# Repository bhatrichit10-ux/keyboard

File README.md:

# keyboard
my own very little keyboard!

i think i need a new keyboard, so whynot make a new one. hehehe

Well, its my first ever keyboard after i made my micropad. (Using qmk for first time aswell)
## Features
- 60% keyboard - 60 keys
- made using qmk
- uses pi pico
- simple matrix design
- easy to recreate

## Schematics
Matrix: <br>
 <br>
Microcontroller: <br>
 <br>

## PCB Design

### PCB Checkout
<br>
<br>

```
Q: Why did i use Robu instead of JLCPCB or SEEED STUDIO FUSION?
A: I live in India and, Robu might be expensive at first but actually it is alot cheaper! Shipping costs to me from JLCPCB and SEEEDSTUDIO FUSION are around $15-$30. Whereas at a little expensive cost, i can get from Robu which is India based and avoid customs as well!

Also my home is like in a region where its harder to ship stuff so maybe robu might also charge extra
```

## CAD 
Case with PCB: <br>
 <br>
 <br>
 <br>
 <br>

## Firmware
I made the firmware using QMK. And compiled it in `firmware` directory

# BOM

|Name                                                          |Purpose         |Quantity|Total Cost (USD)|Distributor   |
|--------------------------------------------------------------|----------------|--------|----------------|--------------|
|RPI Pico                                                      |The brain       |1       |4.47            |RObu.in       |
|Diodes ( Pack of 70)                                          |Matrix Working  |7       |1.16            |Stacks KB     |
|PCB                                                           |Connect stuff   |1       |50.50           |Robu.in       |
|Counter Strike Printstream Decal Collection Cherry PBT Keycaps|Keycaps         |1       |18.07           |Curiosity Caps|
|Akko Botany Switch (Pack of 45)                               |Main Keyswicthes|2       |23.38           |Stacks KB     |

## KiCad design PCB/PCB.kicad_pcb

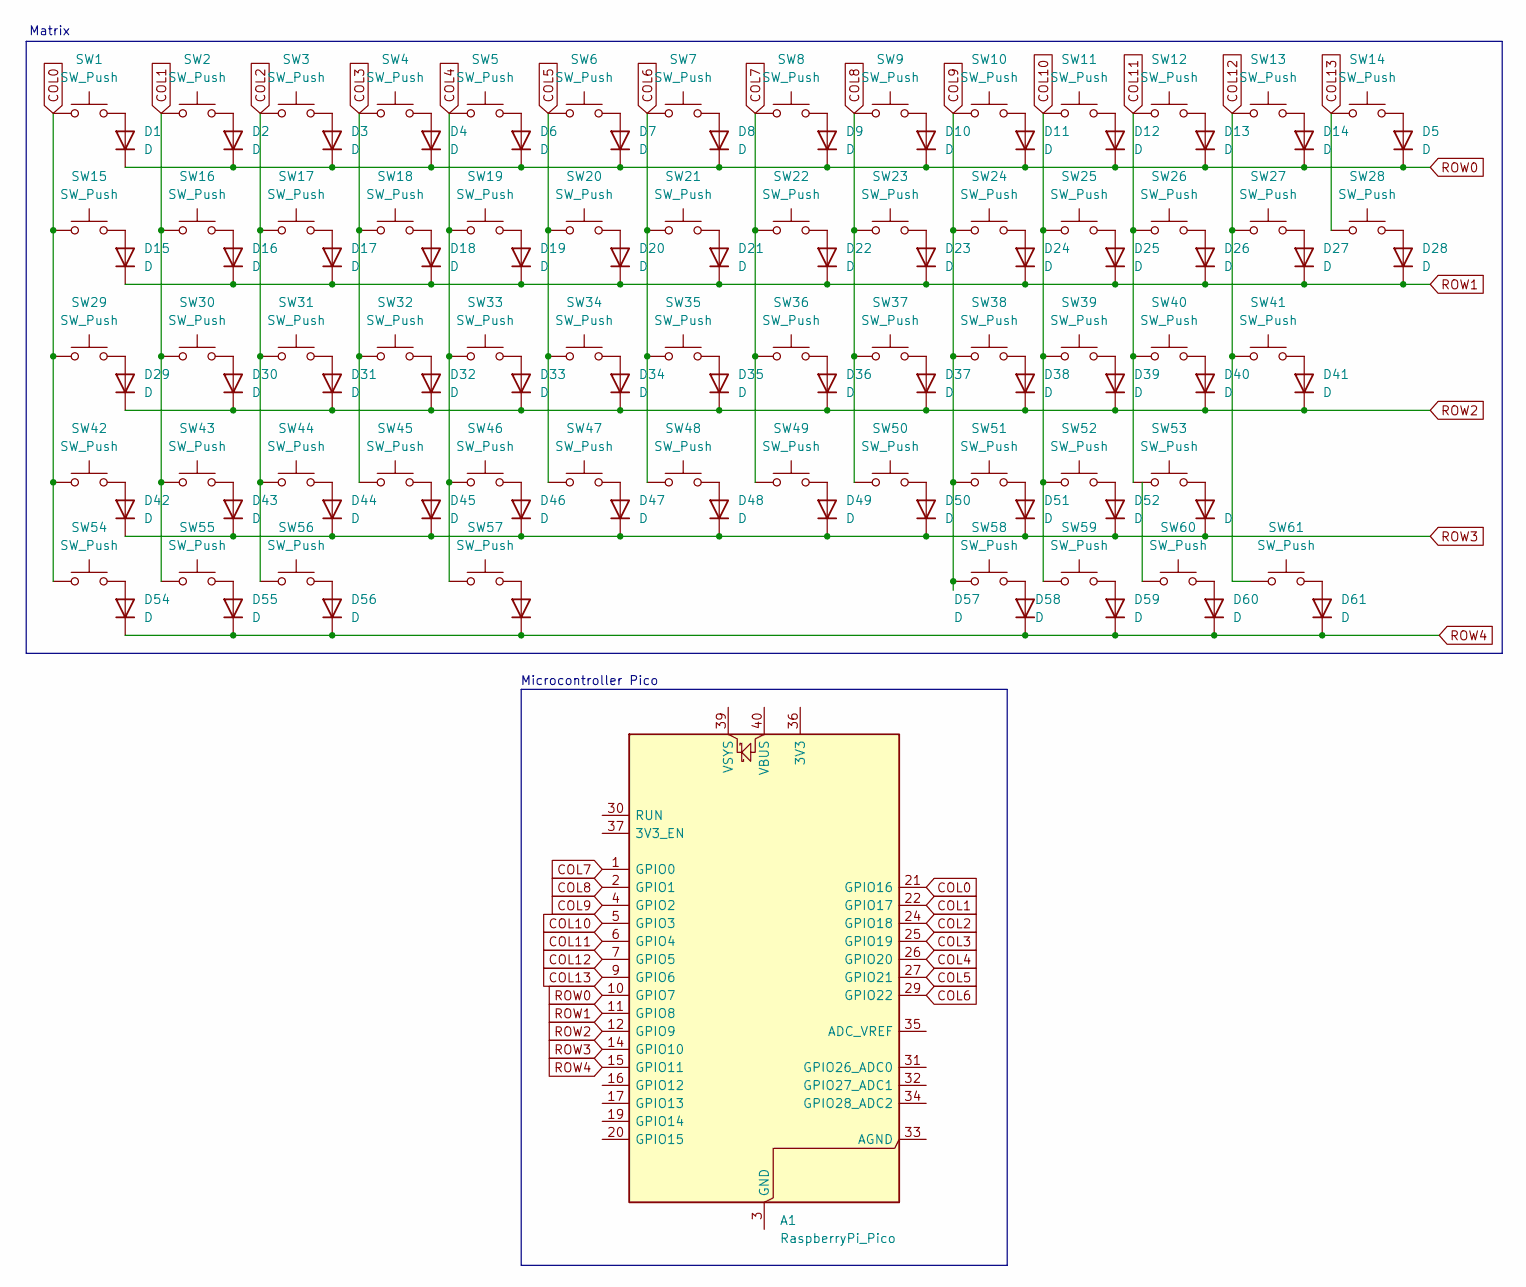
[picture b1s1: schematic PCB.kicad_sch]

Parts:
A1: RaspberryPi_Pico; RaspberryPi_Pico_Common_Unspecified
D1, D2, D3, D4, D5, D6, D7, D8, D9, D10, D11, D12, D13, D14, D15, D16, D17, D18, D19, D20, D21, D22, D23, D24, D25, D26, D27, D28, D29, D30, D31, D32, D33, D34, D35, D36, D37, D38, D39, D40, D41, D42, D43, D44, D45, D46, D47, D48, D49, D50, D51, D52, D53, D54, D55, D56, D57, D58, D59, D60, D61: D; D_DO-35_SOD27_P7.62mm_Horizontal
SW1, SW2, SW3, SW4, SW5, SW6, SW7, SW8, SW9, SW10, SW11, SW12, SW13, SW14, SW15, SW16, SW17, SW18, SW19, SW20, SW21, SW22, SW23, SW24, SW25, SW26, SW27, SW28, SW29, SW30, SW31, SW32, SW33, SW34, SW35, SW36, SW37, SW38, SW39, SW40, SW41, SW42, SW43, SW44, SW45, SW46, SW47, SW48, SW49, SW50, SW51, SW52, SW53, SW54, SW55, SW56, SW57, SW58, SW59, SW60, SW61: SW_Push; SW_Cherry_MX_1.00u_PCB

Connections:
COL0: A1.21 (GPIO16), SW1.1, SW15.1, SW29.1, SW42.1, SW54.1
COL1: A1.22 (GPIO17), SW2.1, SW16.1, SW30.1, SW43.1, SW55.1
COL2: A1.24 (GPIO18), SW3.1, SW17.1, SW31.1, SW44.1, SW56.1
COL3: A1.25 (GPIO19), SW4.1, SW18.1, SW32.1, SW45.1
COL4: A1.26 (GPIO20), SW5.1, SW19.1, SW33.1, SW46.1, SW57.1
COL5: A1.27 (GPIO21), SW6.1, SW20.1, SW34.1, SW47.1
COL6: A1.29 (GPIO22), SW7.1, SW21.1, SW35.1, SW48.1
COL7: A1.1 (GPIO0), SW8.1, SW22.1, SW36.1, SW49.1
COL8: A1.2 (GPIO1), SW9.1, SW23.1, SW37.1, SW50.1
COL9: A1.4 (GPIO2), SW10.1, SW24.1, SW38.1, SW51.1, SW58.1
COL10: A1.5 (GPIO3), SW11.1, SW25.1, SW39.1, SW52.1, SW59.1
COL11: A1.6 (GPIO4), SW12.1, SW26.1, SW40.1, SW53.1
COL12: A1.7 (GPIO5), SW13.1, SW27.1, SW41.1, SW61.1
COL13: A1.9 (GPIO6), SW14.1, SW28.1
unnamed: A1.3 (GND), A1.8 (GND), A1.13 (GND), A1.18 (GND), A1.23 (GND), A1.28 (GND), A1.38 (GND)
unnamed: D1.2 (A), SW1.2
unnamed: D2.2 (A), SW2.2
unnamed: D3.2 (A), SW3.2
unnamed: D4.2 (A), SW4.2
unnamed: D5.2 (A), SW14.2
unnamed: D6.2 (A), SW5.2
unnamed: D7.2 (A), SW6.2
unnamed: D8.2 (A), SW7.2
unnamed: D9.2 (A), SW8.2
unnamed: D10.2 (A), SW9.2
unnamed: D11.2 (A), SW10.2
unnamed: D12.2 (A), SW11.2
unnamed: D13.2 (A), SW12.2
unnamed: D14.2 (A), SW13.2
unnamed: D15.2 (A), SW15.2
unnamed: D16.2 (A), SW16.2
unnamed: D17.2 (A), SW17.2
unnamed: D18.2 (A), SW18.2
unnamed: D19.2 (A), SW19.2
unnamed: D20.2 (A), SW20.2
unnamed: D21.2 (A), SW21.2
unnamed: D22.2 (A), SW22.2
unnamed: D23.2 (A), SW23.2
unnamed: D24.2 (A), SW24.2
unnamed: D25.2 (A), SW25.2
unnamed: D26.2 (A), SW26.2
unnamed: D27.2 (A), SW27.2
unnamed: D28.2 (A), SW28.2
unnamed: D29.2 (A), SW29.2
unnamed: D30.2 (A), SW30.2
unnamed: D31.2 (A), SW31.2
unnamed: D32.2 (A), SW32.2
unnamed: D33.2 (A), SW33.2
unnamed: D34.2 (A), SW34.2
unnamed: D35.2 (A), SW35.2
unnamed: D36.2 (A), SW36.2
unnamed: D37.2 (A), SW37.2
unnamed: D38.2 (A), SW38.2
unnamed: D39.2 (A), SW39.2
unnamed: D40.2 (A), SW40.2
unnamed: D41.2 (A), SW41.2
unnamed: D42.2 (A), SW42.2
unnamed: D43.2 (A), SW43.2
unnamed: D44.2 (A), SW44.2
unnamed: D45.2 (A), SW45.2
unnamed: D46.2 (A), SW46.2
unnamed: D47.2 (A), SW47.2
unnamed: D48.2 (A), SW48.2
unnamed: D49.2 (A), SW49.2
unnamed: D50.2 (A), SW50.2
unnamed: D51.2 (A), SW51.2
unnamed: D52.2 (A), SW52.2
unnamed: D53.2 (A), SW53.2
unnamed: D54.2 (A), SW54.2
unnamed: D55.2 (A), SW55.2
unnamed: D56.2 (A), SW56.2
unnamed: D57.2 (A), SW57.2
unnamed: D58.2 (A), SW58.2
unnamed: D59.2 (A), SW59.2
unnamed: D60.2 (A), SW60.1
unnamed: D61.2 (A), SW61.2
ROW0: A1.10 (GPIO7), D1.1 (K), D2.1 (K), D3.1 (K), D4.1 (K), D5.1 (K), D6.1 (K), D7.1 (K), D8.1 (K), D9.1 (K), D10.1 (K), D11.1 (K), D12.1 (K), D13.1 (K), D14.1 (K)
ROW1: A1.11 (GPIO8), D15.1 (K), D16.1 (K), D17.1 (K), D18.1 (K), D19.1 (K), D20.1 (K), D21.1 (K), D22.1 (K), D23.1 (K), D24.1 (K), D25.1 (K), D26.1 (K), D27.1 (K), D28.1 (K)
ROW2: A1.12 (GPIO9), D29.1 (K), D30.1 (K), D31.1 (K), D32.1 (K), D33.1 (K), D34.1 (K), D35.1 (K), D36.1 (K), D37.1 (K), D38.1 (K), D39.1 (K), D40.1 (K), D41.1 (K)
ROW3: A1.14 (GPIO10), D42.1 (K), D43.1 (K), D44.1 (K), D45.1 (K), D46.1 (K), D47.1 (K), D48.1 (K), D49.1 (K), D50.1 (K), D51.1 (K), D52.1 (K), D53.1 (K)
ROW4: A1.15 (GPIO11), D54.1 (K), D55.1 (K), D56.1 (K), D57.1 (K), D58.1 (K), D59.1 (K), D60.1 (K), D61.1 (K)

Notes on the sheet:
Matrix
Microcontroller Pico

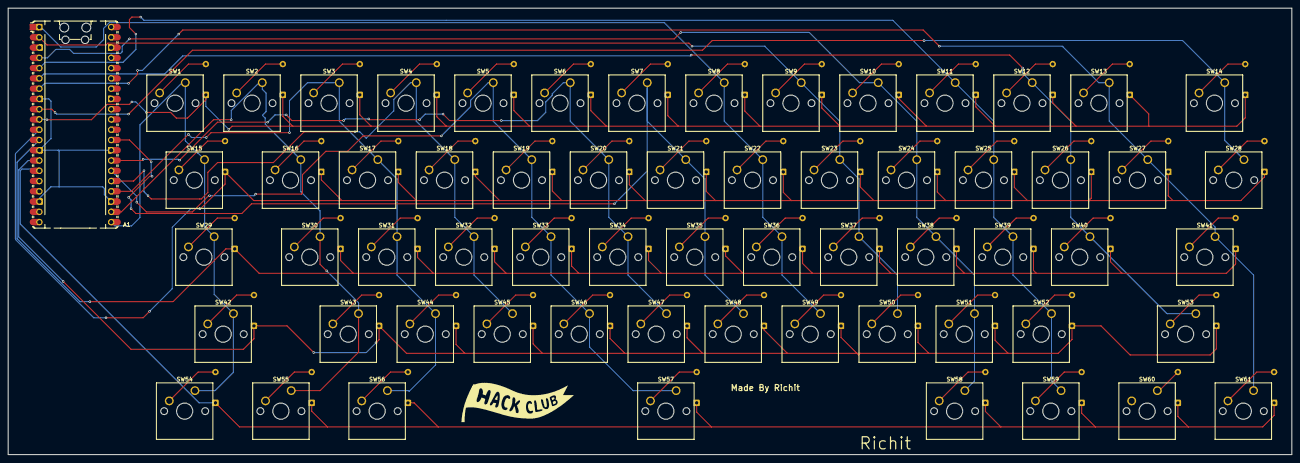
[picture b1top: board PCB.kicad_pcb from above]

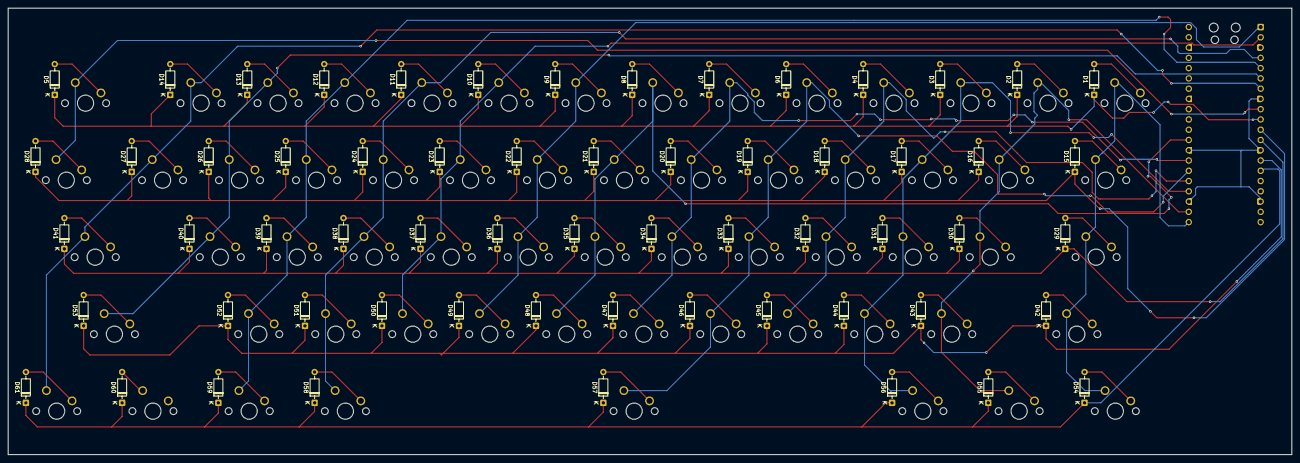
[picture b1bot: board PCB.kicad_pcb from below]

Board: 2 copper layers, 317.6 x 110.4 mm, 123 parts (61 on the bottom side), 81 nets.

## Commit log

2026-03-13 Made schematics
2026-03-14 Added PCB
2026-03-16 Mar 16, 2026, 4:56 PM
2026-03-16 Ready to Ship
2026-03-16 Update BOM.csv with new diode pricing and links
2026-03-16 Update BOM.csv with note clarification
2026-03-22 Ready to SHip!
2026-03-25 With Gerber
2026-03-30 Ship time maybe
2026-03-31 USE LFS ON STEP/STL
2026-03-31 USE LFS ON STEP/STL again
2026-03-31 Remove obsolete files related to PCB design and logging
    - Deleted gerber.zip as it is no longer needed.
    - Removed kbplacer.log which contained outdated plugin information.
    - Cleared lock files (~PCB.kicad_sch.lck and ~_autosave-PCB.kicad_pcb.lck) to prevent conflicts.
2026-03-31 Configure Git LFS for 3D files
2026-03-31 add desc
2026-04-01 stuff: rts
2026-04-25 Ready to Ship #3
2026-04-25 [ImgBot] Optimize images
    *Total -- 1,729.27kb -> 1,141.10kb (34.01%)
    /images/pico.png -- 17.66kb -> 6.77kb (61.65%)
    /images/matrix.png -- 34.10kb -> 15.27kb (55.21%)
    /images/assembly.png -- 350.71kb -> 208.28kb (40.61%)
    /images/pcbd.png -- 84.02kb -> 51.91kb (38.21%)
    /images/3dv.png -- 326.53kb -> 202.30kb (38.04%)
2026-04-26 fixed lfs
2026-04-28 Ready to ship finaly
